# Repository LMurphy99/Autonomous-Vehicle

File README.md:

# Autonomous-Vehicle
 Vehicle which can localise and approach skittles.

Each sub-system has its own folder or archive in the main directory.

For the LIDAR, file of import is "main.c", which details sub-system functionality and all user-made content. Other files were generated by STMCUBE IDE.

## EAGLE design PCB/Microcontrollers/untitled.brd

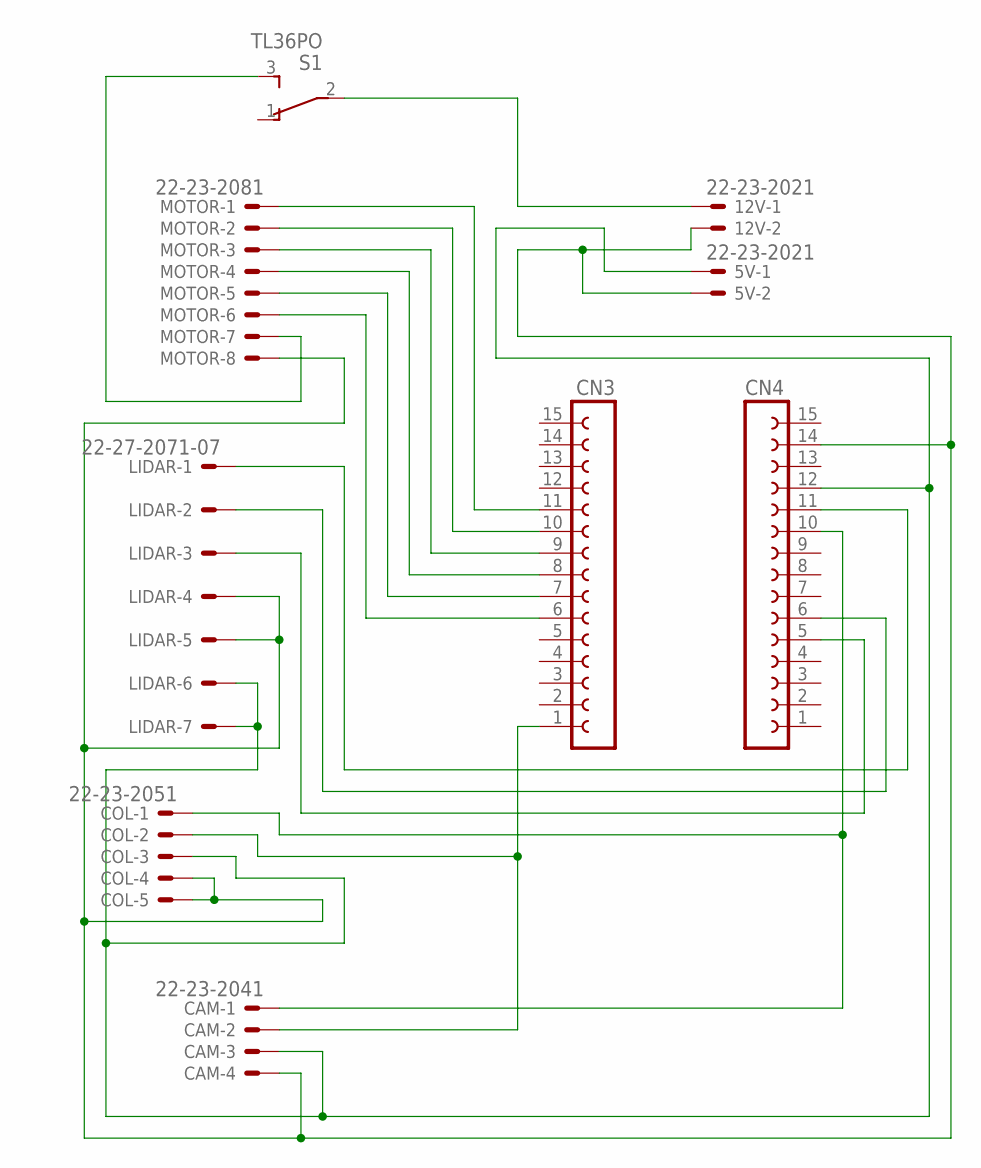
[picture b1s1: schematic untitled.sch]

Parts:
5V, 12V: 22-23-2021
CAM: 22-23-2041
CN3, CN4: FE15-1; FE15
COL: 22-23-2051
LIDAR: 22-27-2071-07; 6410-07
MOTOR: 22-23-2081
S1: TL36PO; TL3XPO

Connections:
unnamed: 5V.2, 12V.2, CAM.4, CN4.14, COL.4, COL.5, LIDAR.4, LIDAR.5, MOTOR.8
unnamed: 5V.1, CAM.3, CN4.12, COL.3, LIDAR.6, LIDAR.7
unnamed: CN3.11, MOTOR.1
unnamed: CN3.9, MOTOR.3
unnamed: CN3.8, MOTOR.4
unnamed: MOTOR.7, S1.3 (S)
unnamed: 12V.1, S1.2
unnamed: CN3.7, MOTOR.5
unnamed: CN3.6, MOTOR.6
unnamed: CN4.11, LIDAR.1
unnamed: CN4.6, LIDAR.2
unnamed: CN4.5, LIDAR.3
unnamed: CAM.1, CN4.10, COL.1
unnamed: CAM.2, CN3.1, COL.2
unnamed: CN3.10, MOTOR.2

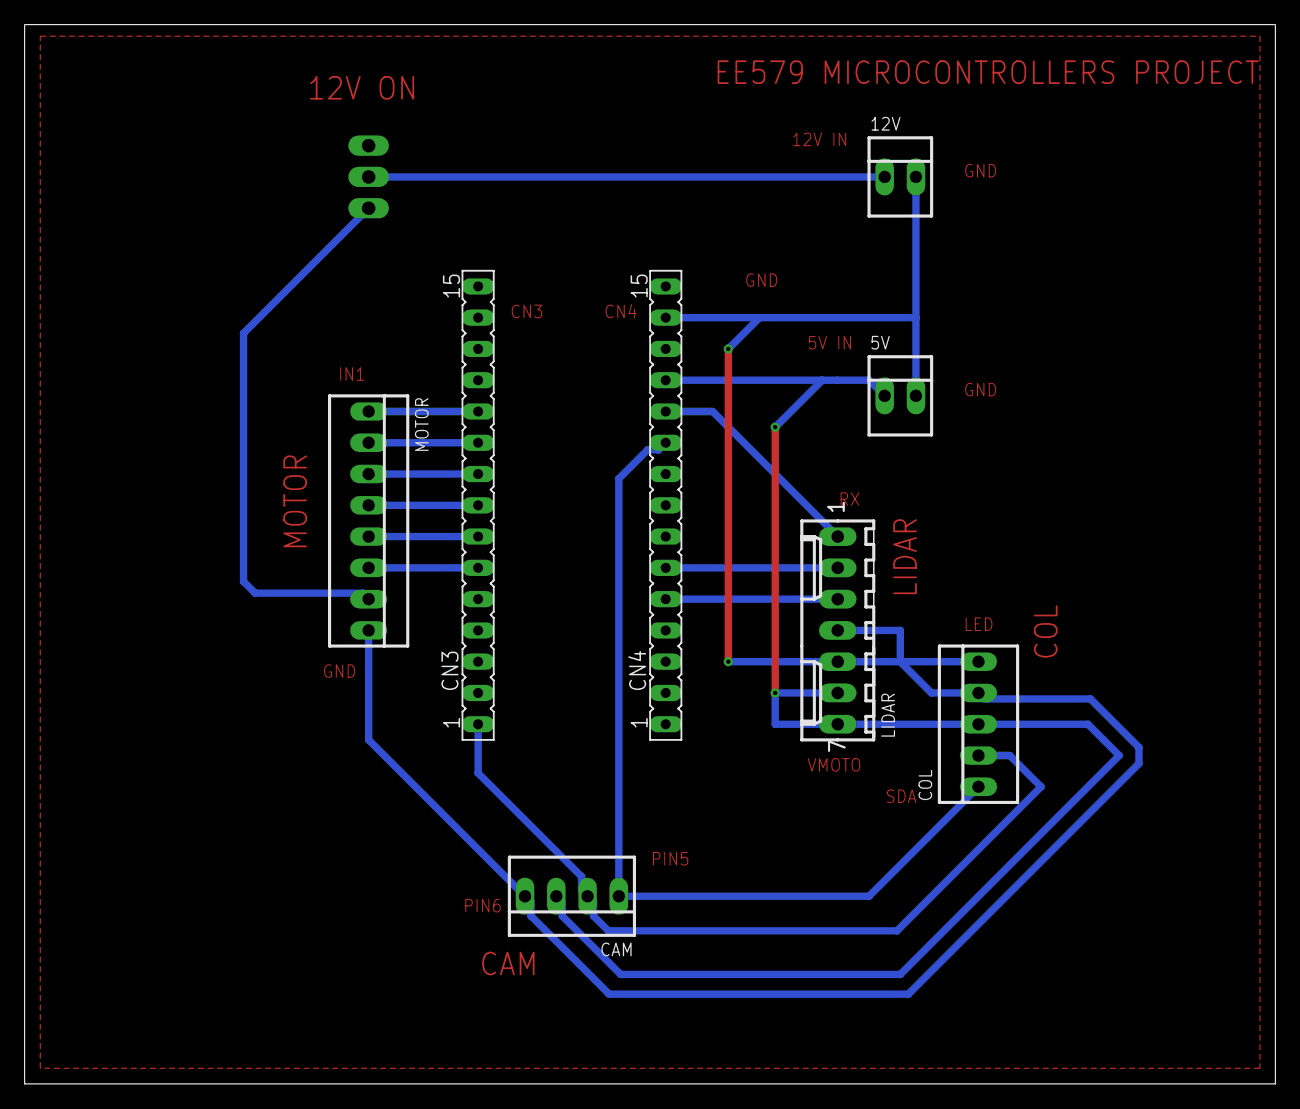
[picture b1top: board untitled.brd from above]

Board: 2 copper layers, 101.6 x 86.0 mm, 9 parts (1 on the bottom side), 15 nets.

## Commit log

2020-05-10 Long-Range Localisation
    Includes and Source files for Long-Range Localisation
2020-05-10 Motor Controller Code
2020-05-13 test file changes
